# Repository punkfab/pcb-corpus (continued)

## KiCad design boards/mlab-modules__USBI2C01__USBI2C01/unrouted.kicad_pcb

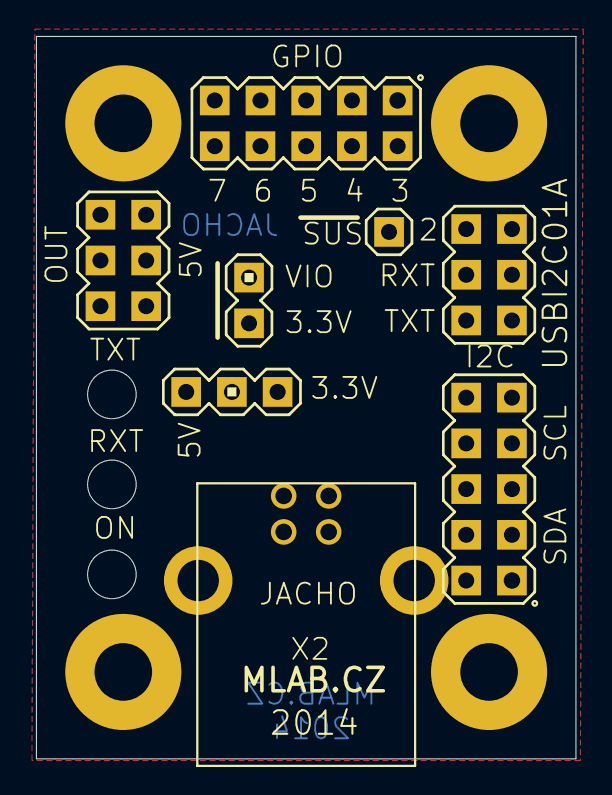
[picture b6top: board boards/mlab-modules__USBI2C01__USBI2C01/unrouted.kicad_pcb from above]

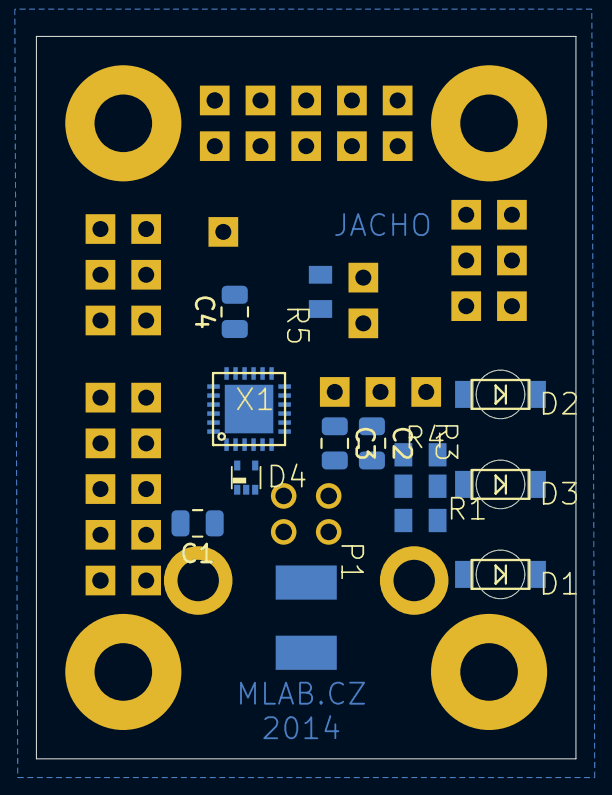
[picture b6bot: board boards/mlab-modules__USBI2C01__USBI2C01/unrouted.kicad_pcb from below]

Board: 2 copper layers, 30.0 x 40.1 mm, 26 parts (14 on the bottom side), 24 nets, no tracks yet.

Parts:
C1: 1uF; C_0805_2012Metric
C2: 10uF; C_0805_2012Metric
C3: 100nF; C_0805_2012Metric
C4: 4u7; C_0805_2012Metric
D1: ZELENA; 1206_2
D2, D3: CERVENA; 1206_2
D4: SP1001-04XTG; SOT553
P1: 750mA; 1812
R1, R3, R4: 470R; 0805
R5: 4k7; 0805
SV1: MA02-1
SV2, SV5: MA05-2
SV3: MA03-1
SV4, SV6: MA03-2
SV7: MA01-1
X1: CP2112; QFN-24
X2: USB_B
X3, X4, X5, X6: SROUB3M

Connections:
+3.3V: C2.1, C3.1, R3.1, R4.1, SV1.1, SV3.1, X1.P$6 (VDD)
+5V: C1.1, D4.1, P1.2, R1.2, SV3.3, SV6.3, SV6.4, X1.P$7 (REGIN), X1.P$8 (VBUS)
GND: C1.2, C2.2, C3.2, C4.2, D1.K (C), D4.2, SV2.1, SV2.2, SV2.9, SV2.10, SV6.1, SV6.2, SV6.5, SV6.6, X1.P$2 (GND), X1.P$25 (GND), X2.4 (GND), X2.GND, X2.GND2 (GND), X3.P$1, X4.P$1, X5.P$1, X6.P$1
unnamed: C4.1, X1.P$16 (VPP)
unnamed: D1.A, R1.1
unnamed: D2.A, R4.2
unnamed: D2.K (C), SV4.1, SV4.2, X1.P$23 (GPIO0-TXT)
unnamed: D3.A, R3.2
unnamed: D4.4, X1.P$4 (D-), X2.2 (DATA-)
unnamed: D4.5, X1.P$3 (D+), X2.3 (DATA+)
unnamed: P1.1, X2.1 (+5V)
unnamed: R5.1, X1.P$9 (/RST)
unnamed: R5.2, SV1.2, X1.P$5 (VIO)
unnamed: SV2.5, SV2.6, SV3.2
unnamed: SV5.1, SV5.2, X1.P$20 (GPIO3)
unnamed: SV7.1, X1.P$17 (/SUSPEND)
unnamed: SV2.3, SV2.4, X1.P$1 (SDA)
unnamed: SV5.9, SV5.10, X1.P$12 (GPIO7-CLK)
unnamed: SV5.7, SV5.8, X1.P$13 (GPIO6)
unnamed: SV5.5, SV5.6, X1.P$14 (GPIO5)
unnamed: SV5.3, SV5.4, X1.P$15 (GPIO4)
unnamed: SV4.5, SV4.6, X1.P$21 (GPIO2)
unnamed: D3.K (C), SV4.3, SV4.4, X1.P$22 (GPIO1-RXT)
unnamed: SV2.7, SV2.8, X1.P$24 (SCL)
